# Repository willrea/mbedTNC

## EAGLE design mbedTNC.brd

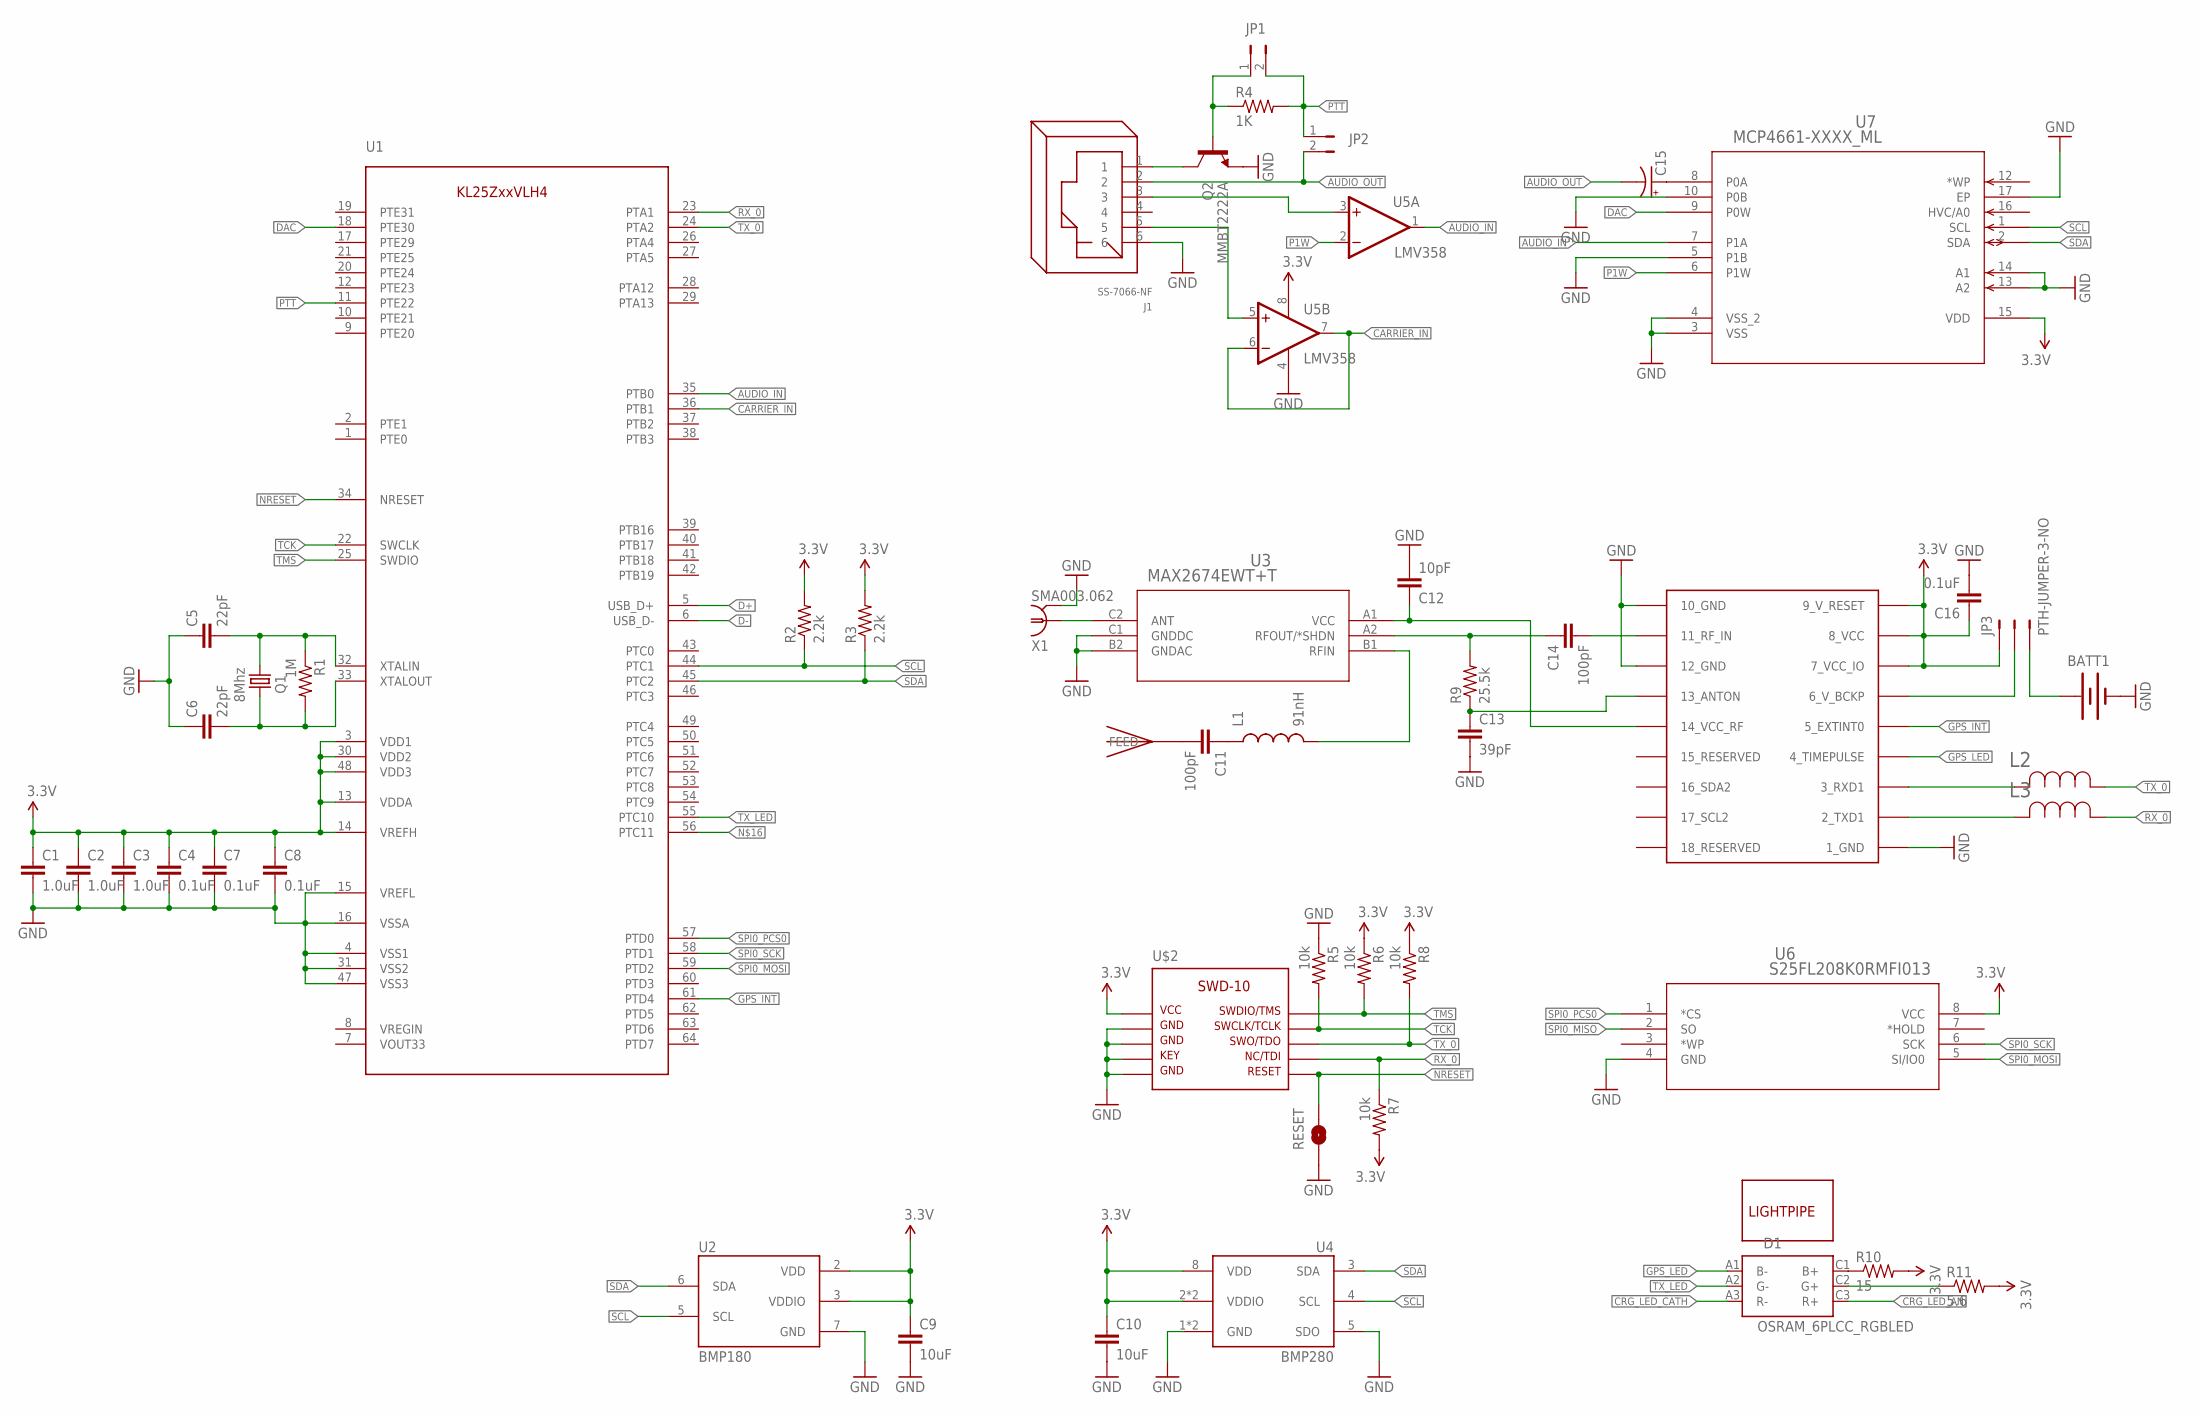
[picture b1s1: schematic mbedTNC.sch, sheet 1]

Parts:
BATT1: BK-890; BATTCON_12MMPC; MPN BK-890
C1, C2, C3: 1.0uF; 0603-CAP; MPN EMK107B7105KA-T
C4, C7, C8, C16: 0.1uF; 0603-CAP; MPN GRM188R71C104KA01D
C5, C6: 22pF; 0603-CAP; MPN C1608C0G1H220J080AA
C9, C10: 10uF; 0805; MPN CC0805KKX5R6BB106
C11, C14: 100pF; 0603-CAP; MPN CL10B101KB8NNNC
C12: 10pF; 0603-CAP; MPN CL10C100CB8NNNC
C13: 39pF; 0603-CAP; MPN CL10C390JB8NNNC
C15: UWX1C100MCL2GB; PCAP_4X5.4-ELECT; MPN UWX1C100MCL2GB
D1: OSRAM_6PLCC_RGBLED; LRTB-GFTM; MPN LRTBGFTM-ST7-1+VV9-29+Q5R
J1: SS-7066-NF; MPN SS-7066-NF
JP1, JP2: JUMPER-PTH-2-NO; PTH-JUMPER-2-NO_NO_SILK
JP3: PTH-JUMPER-3-NO
L1: 91nH; 0603; MPN LQW18AN91NJ00D
L2, L3: BLM18HG102SN1D; IND_BLM18_0603; MPN BLM18HG102SN1D
Q1: 8Mhz; CRYSTAL_5X3.2; MPN 7A-8.000MAAJ-T
Q2: MMBT2222A; SOT23-3; MPN MMBT2222ALT3G
R1: 1M; 0603-RES; MPN RMCF0603FT1M00
R2, R3: 2.2k; 0603-RES; MPN RMCF0603JT2K20
R4: 1K; 0603-RES; MPN RMCF0603JT1K00
R5, R6, R7, R8: 10k; 0603-RES; MPN RNCP0603FTD10K0
R9: 25.5k; 0603-RES; MPN RMCF0603FT25K5
R10: 15; 0603-RES; MPN RMCF0603JT15R0
R11: 5.6; 0603-RES; MPN RMCF0603FT5R60
RESET: JUMPER-PAD-2-NOYES_SILK; PAD-JUMPER-2-NO_YES_SILK
U1: MKL25ZXXVLH4; 64-LQFP; MPN MKL25ZXXVLH4
U2: BMP180
U3: MAX2674EWT+T; 21-0217D_W61B1-1; MPN MAX2674EWT+T
U4: BMP280
U5: LMV358; DDU8-M; MPN LMV358IDDUR
U6: S25FL208K0RMFI013; SO-8_SOA008; MPN S25FL208K0RMFI013
U7: MCP4661-XXXX_ML; QFN16_4X4MC; MPN MCP4661T-103E/ML
U$1: JTI_ANTENNA-1575AT43A40; MPN 1575AT43A0040E
U$2: SWD-10; M50-3600542
U$3: UBLOX_MAX; MPN MAX-7Q
U$4: VLP-ZZZ-X; MPN VLP-500-F
X1: SMA003.062; MPN consma003.062

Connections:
3.3V: C1.1, C2.1, C3.1, C4.1, C7.1, C8.1, C9.1, C10.1, C16.1, JP3.1, R2.2, R3.2, R6.1, R7.2, R8.1, R10.2, R11.2, U1.3 (VDD1), U1.13 (VDDA), U1.14 (VREFH), U1.30 (VDD2), U1.48 (VDD3), U2.2 (VDD), U2.3 (VDDIO), U4.2 (VDDIO), U4.6 (VDDIO), U4.8 (VDD), U5.8 (V+), U6.8 (VCC), U7.15 (VDD), U$2.P$1 (1), U$3.7_VCC_IO, U$3.8_VCC, U$3.9_V_RESET; also elsewhere on the board
AUDIO_IN: U1.35 (PTB0), U5.1 (OUT), U7.7 (P1A)
AUDIO_OUT: C15.2 (-), J1.2, JP2.2
CARRIER_IN: U1.36 (PTB1), U5.6 (-IN), U5.7 (OUT)
CRG_LED_AN: D1.C3 (R+); also elsewhere on the board
CRG_LED_CATH: D1.A3 (R-); also elsewhere on the board
D+: U1.5 (USB_D+); also elsewhere on the board
D-: U1.6 (USB_D-); also elsewhere on the board
DAC: U1.18 (PTE30), U7.9 (P0W)
GND: BATT1.C1 (-), C1.2, C2.2, C3.2, C4.2, C5.1, C6.1, C7.2, C8.2, C9.2, C10.2, C12.2, C13.2, C16.2, J1.6, Q2.2 (E), R5.1, RESET.1, U1.4 (VSS1), U1.15 (VREFL), U1.16 (VSSA), U1.31 (VSS2), U1.47 (VSS3), U2.7 (GND), U3.B2 (GNDAC), U3.C1 (GNDDC), U4.1 (GND), U4.5 (SDO), U4.7 (GND), U5.4 (V-), U6.4 (GND), U7.3 (VSS), U7.4 (VSS_2), U7.5 (P1B), U7.10 (P0B), U7.13 (A2), U7.14 (A1), U7.17 (EP), U$2.P$3 (3), U$2.P$5 (5), U$2.P$7 (7), U$2.P$9 (9), U$3.1_GND, U$3.10_GND, U$3.12_GND, X1.C2 (2), X1.C3 (2), X1.C4 (2), X1.C5 (2); also elsewhere on the board
GPS_INT: U1.61 (PTD4), U$3.5_EXTINT0
GPS_LED: D1.A1 (B-), U$3.4_TIMEPULSE
N2: C14.2, U$3.11_RF_IN
unnamed: C11.2, U$1.FEED
unnamed: C14.1, R9.2, U3.A2 (RFOUT/*SHDN)
unnamed: J1.1, Q2.3 (C)
unnamed: L1.2, U3.B1 (RFIN)
unnamed: JP3.2, U$3.6_V_BCKP
unnamed: C12.1, U3.A1 (VCC), U$3.14_VCC_RF
unnamed: C5.2, Q1.P$2 (2), R1.1, U1.32 (XTALIN)
unnamed: C6.2, Q1.P$1 (1), R1.2, U1.33 (XTALOUT)
unnamed: D1.C2 (G+), R11.1
unnamed: D1.C1 (B+), R10.1
unnamed: C11.1, L1.1
unnamed: L2.2, U$3.3_RXD1
unnamed: C15.1 (+), U7.8 (P0A)
unnamed: J1.3, U5.3 (+IN)
unnamed: L3.2, U$3.2_TXD1
unnamed: JP1.1, Q2.1 (B), R4.1
unnamed: J1.5, U5.5 (+IN)
unnamed: U3.C2 (ANT), X1.RF (1)
unnamed: C13.1, R9.1, U$3.13_ANTON
unnamed: BATT1.C2 (+), BATT1.C3 (+), JP3.3
NRESET: RESET.2, U1.34 (NRESET), U$2.P$10 (10)
P1W: U5.2 (-IN), U7.6 (P1W)
PTT: JP1.2, JP2.1, R4.2, U1.11 (PTE22)
RX_0: L3.1, R7.1, U1.23 (PTA1), U$2.P$8 (8)
SCL: R2.1, U1.44 (PTC1), U2.5 (SCL), U4.4 (SCL), U7.1 (SCL)
SDA: R3.1, U1.45 (PTC2), U2.6 (SDA), U4.3 (SDA), U7.2 (SDA)
SPI0_MISO: U6.2 (SO)
SPI0_MOSI: U1.59 (PTD2), U6.5 (SI/IO0)
SPI0_PCS0: U1.57 (PTD0), U6.1 (*CS)
SPI0_SCK: U1.58 (PTD1), U6.6 (SCK)
TCK: R5.2, U1.22 (SWCLK), U$2.P$4 (4)
TMS: R6.2, U1.25 (SWDIO), U$2.P$2 (2)
TX_0: L2.1, R8.2, U1.24 (PTA2), U$2.P$6 (6)
TX_LED: D1.A2 (G-), U1.55 (PTC10)

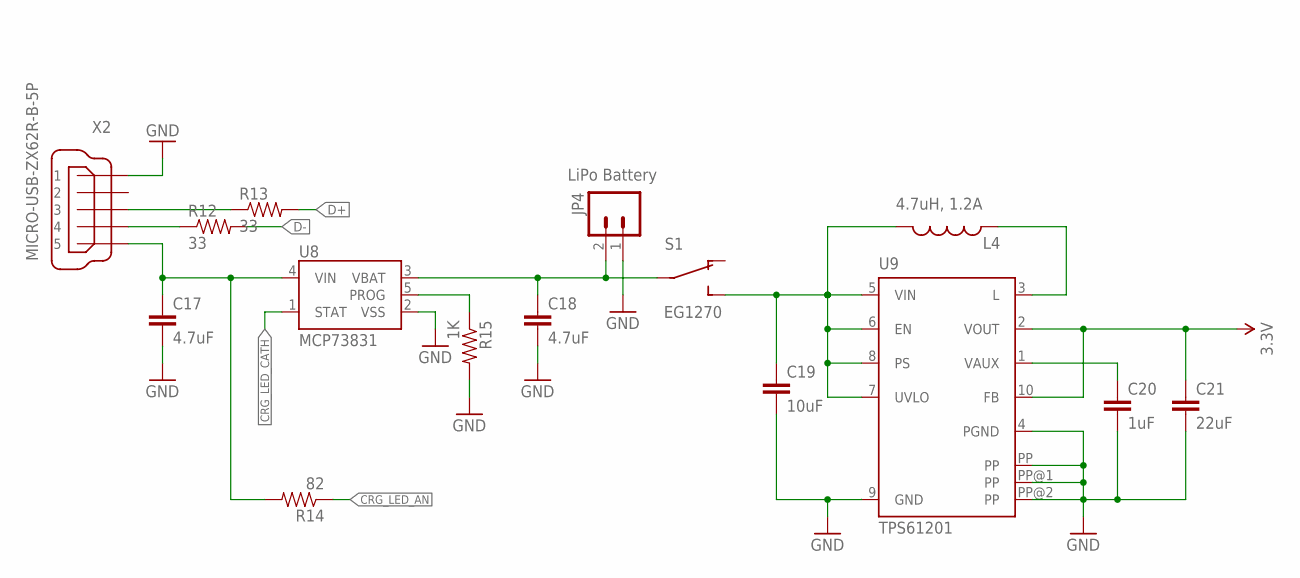
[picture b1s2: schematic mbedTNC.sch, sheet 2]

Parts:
C17, C18: 4.7uF; 0805; MPN CL21B475KOFNNNE
C19: 10uF; 0805; MPN CL21A106KOQNNNE
C20: 1uF; 0603-CAP; MPN EMK107B7105KA-T
C21: 22uF; 1206; MPN CL31A226KOCLFNC
JP4: LiPo Battery; JST-2-SMD; MPN S2B-PH-SM4-TB(LF)(SN)
L4: 4.7uH, 1.2A; CDRH2D09; MPN CDRH2D18/HPNP-4R7NC
R12, R13: 33; 0603-RES; MPN RMCF0603FT33R0
R14: 82; 0603-RES; MPN ESR03EZPJ820
R15: 1K; 0603-RES; MPN RMCF0603JT1K00
S1: EG1270; MPN EG1270
U8: MCP73831; SOT23-5; MPN MCP73831
U9: TPS61201; S-PDSO-N10
X2: MICRO-USB-ZX62R-B-5P; ZX62R-B-5P; MPN ZX62R-B-5P

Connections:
3.3V: C21.1, U9.2 (VOUT), U9.10 (FB); also elsewhere on the board
CRG_LED_AN: R14.1; also elsewhere on the board
CRG_LED_CATH: U8.1 (STAT); also elsewhere on the board
D+: R13.2; also elsewhere on the board
D++: R13.1, X2.3
D-: R12.2; also elsewhere on the board
D--: R12.1, X2.4
GND: C17.2, C18.2, C19.2, C20.2, C21.2, JP4.1, R15.2, U8.2 (VSS), U9.4 (PGND), U9.9 (GND), U9.PP, U9.PP@1 (PP), U9.PP@2 (PP), X2.1; also elsewhere on the board
unnamed: C17.1, R14.2, U8.4 (VIN), X2.5
unnamed: C18.1, JP4.2, S1.P$2, U8.3 (VBAT)
unnamed: L4.P$1 (1), U9.3 (L)
PROG1: R15.1, U8.5 (PROG)
VAUX: C20.1, U9.1 (VAUX)
VIN: C19.1, L4.P$2 (2), S1.P$3 (O2), U9.5 (VIN), U9.6 (EN), U9.7 (UVLO), U9.8 (PS)

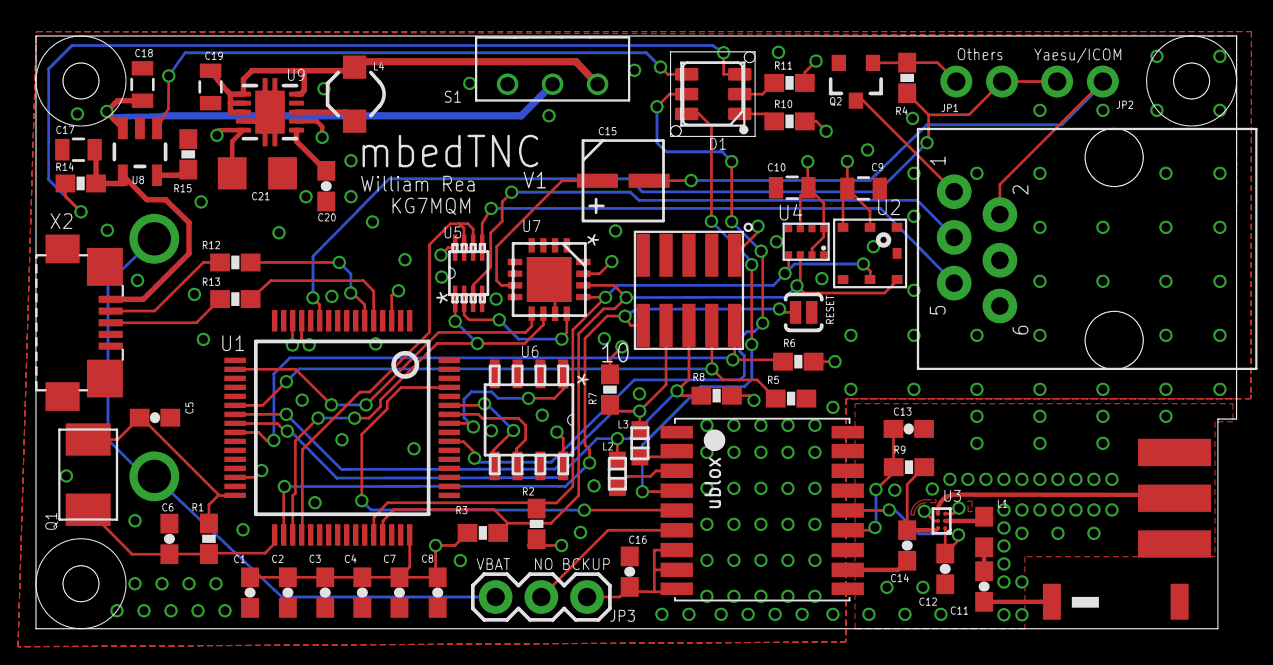
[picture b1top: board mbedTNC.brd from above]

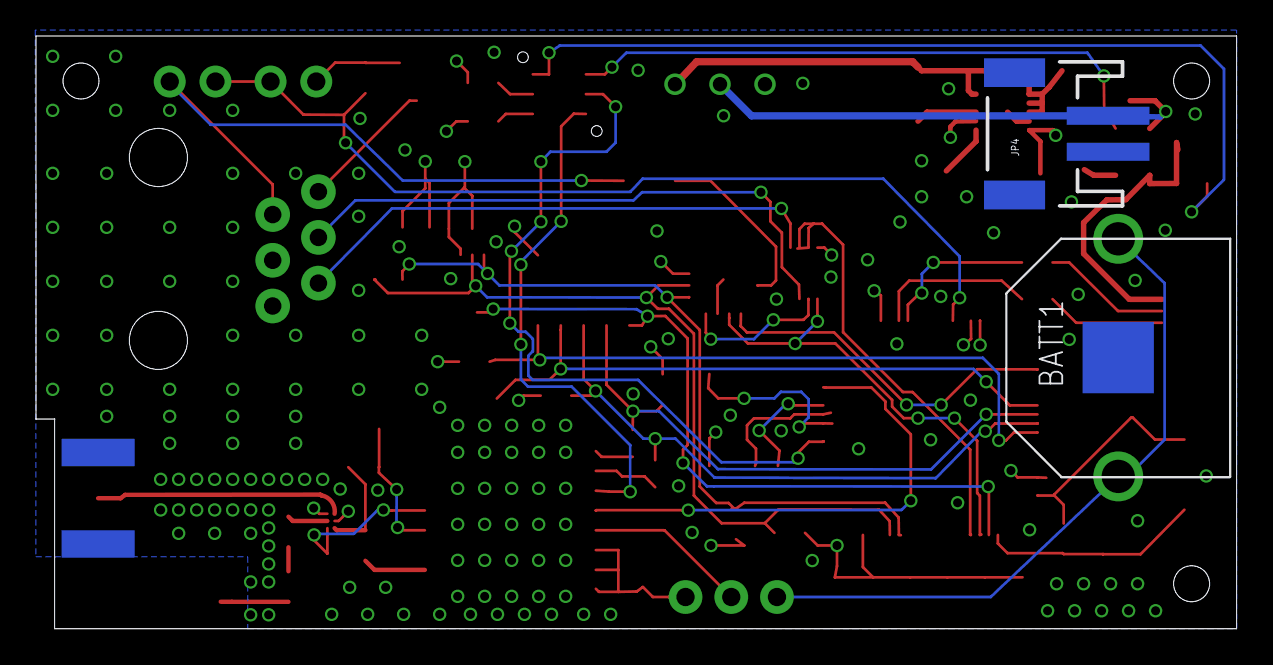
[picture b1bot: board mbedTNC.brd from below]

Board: 4 copper layers, 66.7 x 32.9 mm, 66 parts (2 on the bottom side), 54 nets.

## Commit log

2014-07-17 Initial commit.
2014-07-19 Update
    Added support for Yaesu/Icom radios. Moved components around.
2014-07-22 Update
    Changed to a 2 circuit digipot. Various other changes
2014-08-01 Update.
    Move to 4 layer board. New LNA with internal switch for an active
    external ant. Finalizing parts, moved stuff around.
2014-08-02 Update
    Moved some components around to accommodate case design
2014-08-08 Version 1

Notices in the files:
parts and their libraries:
SparkFun-Capacitors: Licensing: Creative Commons ShareAlike 4.0 International - https://creativecommons.org/licenses/by-sa/4.0
SparkFun-Resistors: Licensing: CC v3.0 Share-Alike You are welcome to use this library for commercial purposes.
